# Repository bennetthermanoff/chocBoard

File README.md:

# chocBoard
PCB, ergogen, kicad files for chocBoard wireless split ergo keyboard
## [Learn more on my website](https://www.hermanoff.dev/content/chocBoard)

This repo contains the files to order a custom PCB for chocBoard, checkout my [zmk fork](https://github.com/xpsKING/zmk) to build firmware!

Read more about chocBoard on my [website](https://hermanoff.dev)

## LICENSE
This repo is attached with Attribution-NonCommercial-ShareAlike 4.0 International Creative Commons License, learn what his means [here](https://creativecommons.org/licenses/by-nc-sa/4.0/).

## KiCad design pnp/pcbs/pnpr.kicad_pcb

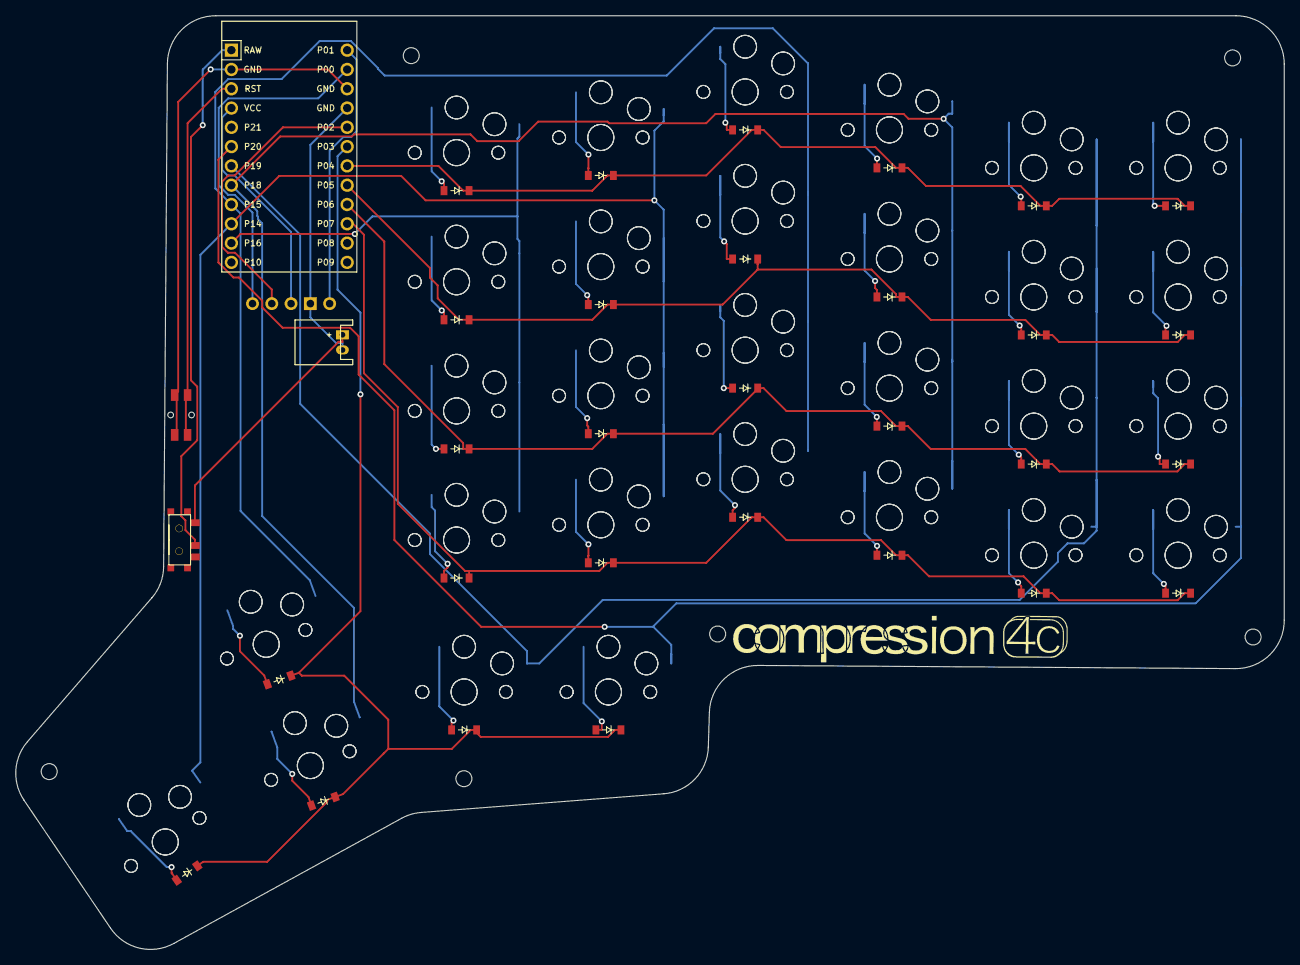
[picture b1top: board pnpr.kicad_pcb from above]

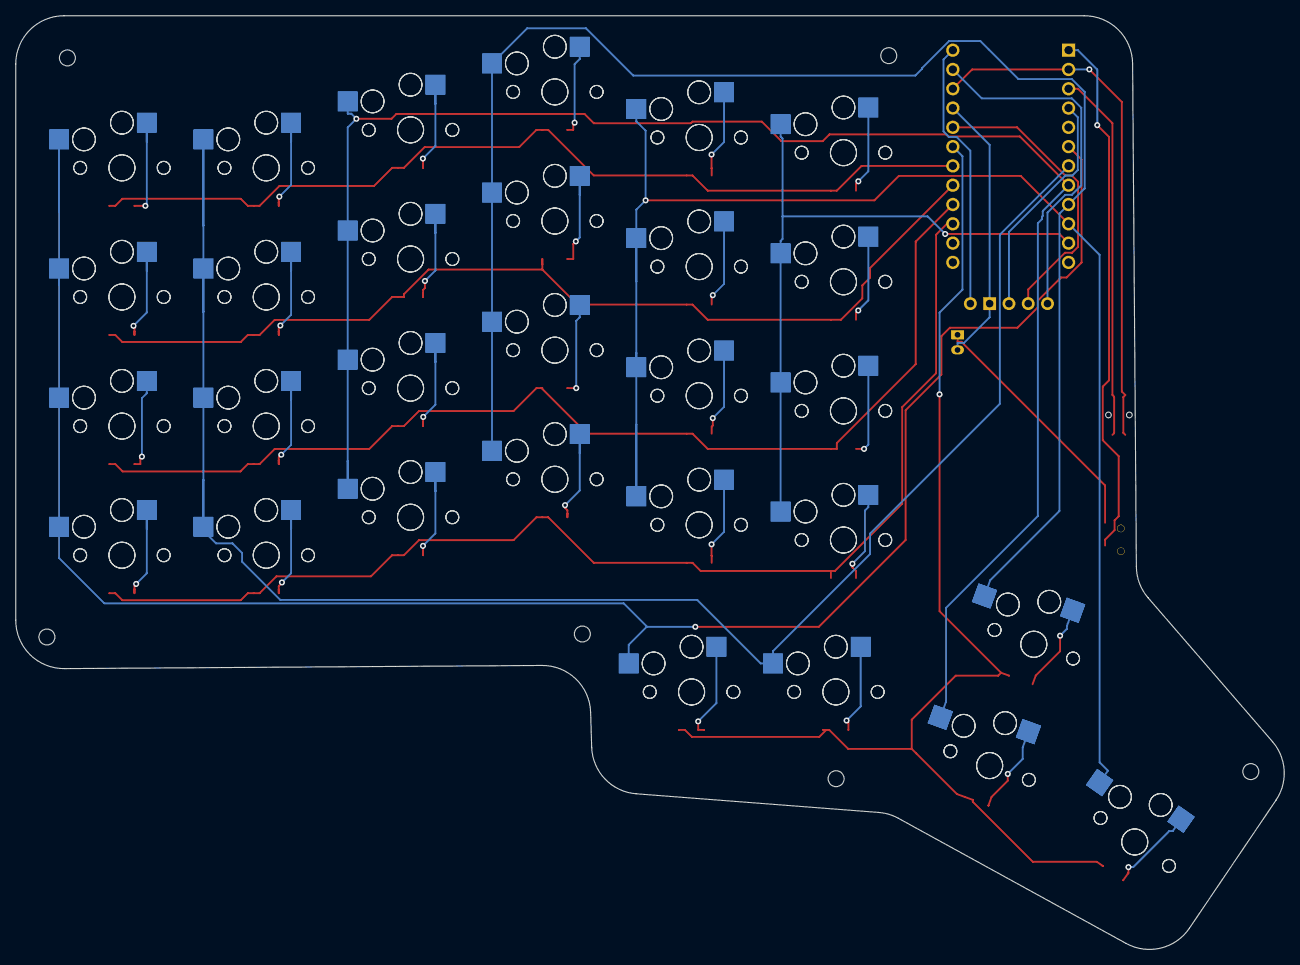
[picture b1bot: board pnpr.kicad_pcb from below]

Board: 2 copper layers, 167.0 x 122.9 mm, 92 parts (29 on the bottom side), 44 nets.

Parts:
D31, D34, D36, D37, D41, D49, D51, D52, D53, D54, D57, D58, D59, D61, D62, D64, D67, D68, D69, D71, D72, D73, D74, D75, D76, D77, D79, D84, D85: ComboDiode
JST1: JST_PH_S2B-PH-K_02x2.00mm_Angled
MCU1: ProMicro
OLED1: OLED; OLED_headers
Panasonic_EVQPUL_EVQPUC: Panasonic_EVQPUL_EVQPUC
S30, S31, S32, S33, S34, S35, S36, S37, S38, S39, S40, S41, S42, S43, S44, S45, S46, S47, S48, S49, S50, S51, S52, S53, S54, S55, S56, S57, S58, S59, S60, S61, S62, S63, S64, S65, S66, S67, S68, S69, S70, S71, S72, S73, S74, S75, S76, S77, S78, S79, S80, S81, S82, S83, S84, S85, S86, S87: PG1350
T1: SPDT_C128955

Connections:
Bplus: JST1.1, T1.1
GND: JST1.2, MCU1.2, MCU1.15, MCU1.16, Panasonic_EVQPUL_EVQPUC.1
P3: D54.1, D57.1, D58.1, D84.1, D85.1, MCU1.18
P4: D37.1, D41.1, D49.1, D53.1, D62.1, D74.1, MCU1.19
P5: D36.1, D52.1, D61.1, D69.1, D73.1, D77.1, MCU1.20
P6: D31.1, D51.1, D64.1, D68.1, D72.1, D76.1, MCU1.21
P7: D34.1, D59.1, D67.1, D71.1, D75.1, D79.1, MCU1.22
P14: MCU1.10, S46.2, S47.2, S48.2, S49.2, S58.2, S75.2, S76.2, S77.2, S78.2, S87.2
P15: MCU1.9, S42.2, S43.2, S44.2, S45.2, S57.2, S71.2, S72.2, S73.2, S74.2, S86.2
P16: MCU1.11, S50.2, S51.2, S52.2, S53.2, S79.2, S80.2, S81.2, S82.2
P18: MCU1.8, S38.2, S39.2, S40.2, S41.2, S56.2, S67.2, S68.2, S69.2, S70.2, S85.2
P19: MCU1.7, S34.2, S35.2, S36.2, S37.2, S55.2, S63.2, S64.2, S65.2, S66.2, S84.2
P20: MCU1.6, S30.2, S31.2, S32.2, S33.2, S54.2, S59.2, S60.2, S61.2, S62.2, S83.2
RAW: MCU1.1, T1.2
RST: MCU1.3, Panasonic_EVQPUL_EVQPUC.2
mirror_far_home: D58.2, S58.1, S87.1
mirror_home_home: D85.2, S56.1, S85.1
mirror_home_top: D57.2, S57.1, S86.1
mirror_index_bottom: D75.2, S46.1, S75.1
mirror_index_home: D76.2, S47.1, S76.1
mirror_index_num: D49.2, S49.1, S78.1
mirror_index_top: D77.2, S48.1, S77.1
mirror_inner_bottom: D79.2, S50.1, S79.1
mirror_inner_home: D51.2, S51.1, S80.1
mirror_inner_num: D53.2, S53.1, S82.1
mirror_inner_top: D52.2, S52.1, S81.1
mirror_middle_bottom: D71.2, S42.1, S71.1
mirror_middle_home: D72.2, S43.1, S72.1
mirror_middle_num: D74.2, S45.1, S74.1
mirror_middle_top: D73.2, S44.1, S73.1
mirror_near1_home: D54.2, S54.1, S83.1
mirror_near2_home: D84.2, S55.1, S84.1
mirror_outer_bottom: D59.2, S30.1, S59.1
mirror_outer_home: D31.2, S31.1, S60.1
mirror_outer_num: D62.2, S33.1, S62.1
mirror_outer_top: D61.2, S32.1, S61.1
mirror_pinky_bottom: D34.2, S34.1, S63.1
mirror_pinky_home: D64.2, S35.1, S64.1
mirror_pinky_num: D37.2, S37.1, S66.1
mirror_pinky_top: D36.2, S36.1, S65.1
mirror_ring_bottom: D67.2, S38.1, S67.1
mirror_ring_home: D68.2, S39.1, S68.1
mirror_ring_num: D41.2, S41.1, S70.1
mirror_ring_top: D69.2, S40.1, S69.1

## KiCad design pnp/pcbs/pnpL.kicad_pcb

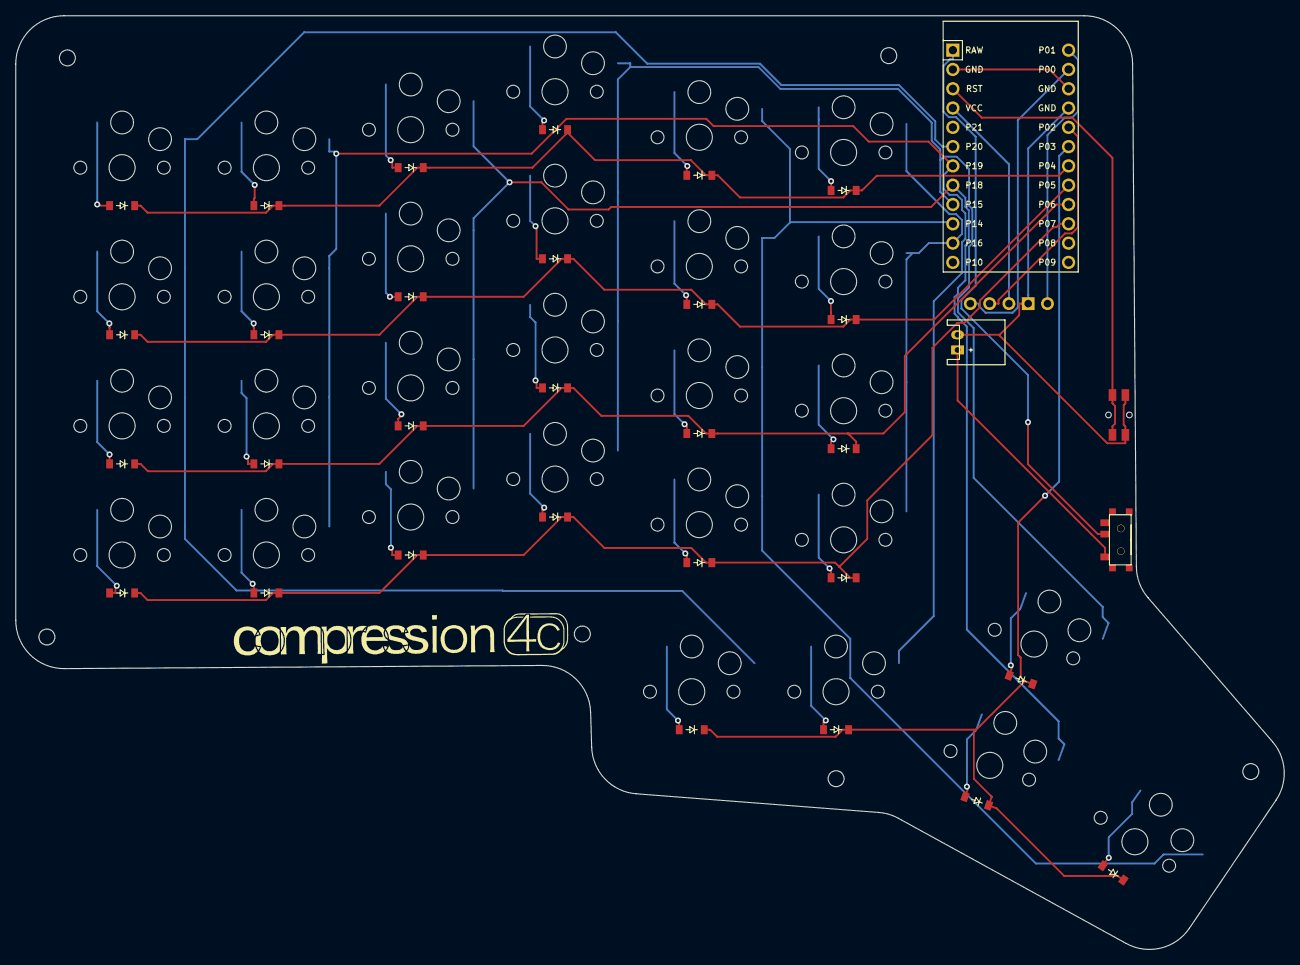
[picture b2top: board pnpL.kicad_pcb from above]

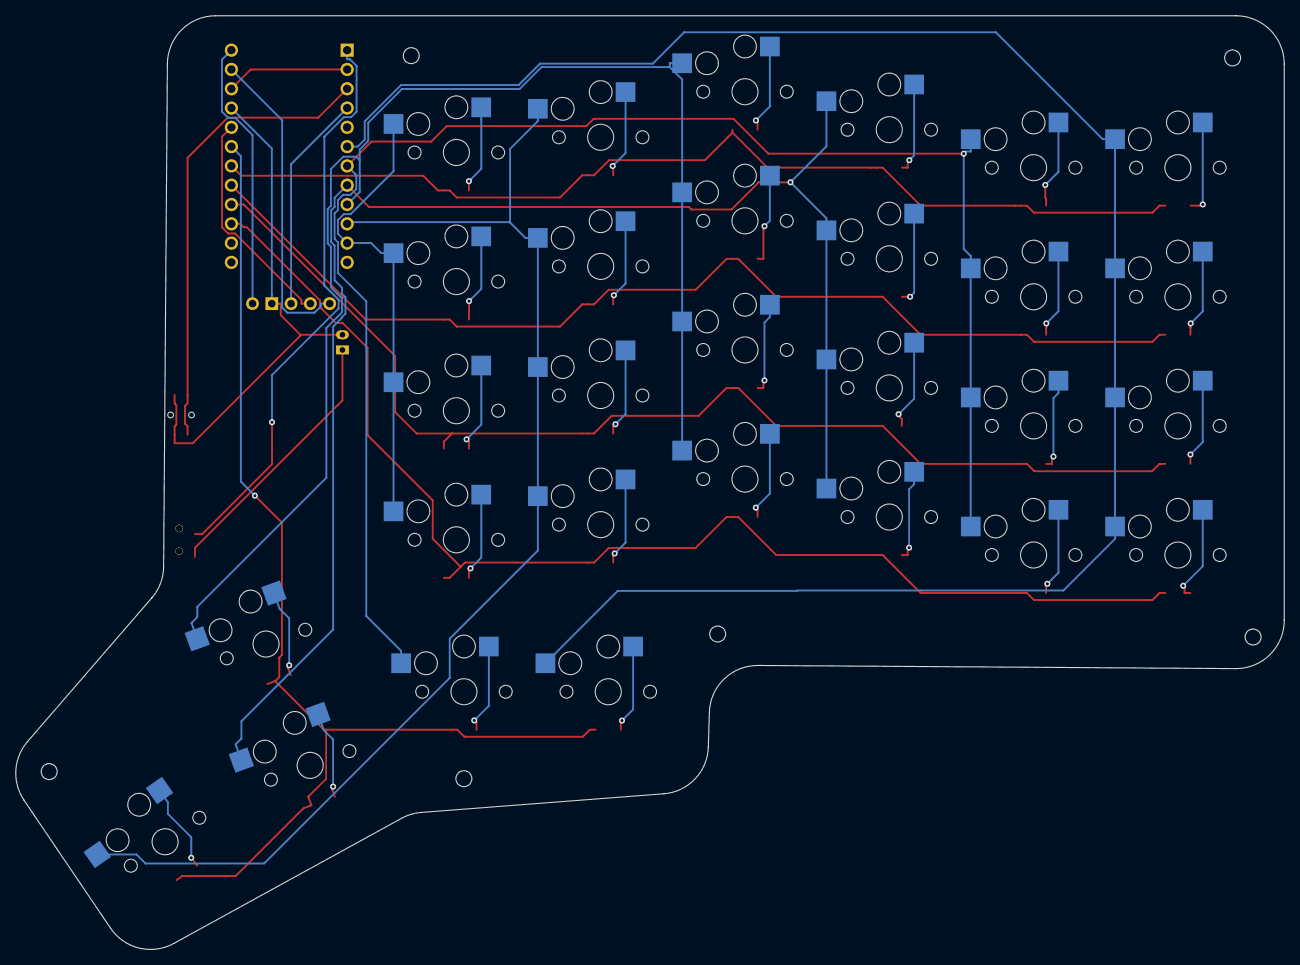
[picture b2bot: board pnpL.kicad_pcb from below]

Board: 2 copper layers, 167.0 x 122.9 mm, 63 parts (29 on the bottom side), 48 nets.

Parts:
D1, D2, D3, D4, D5, D6, D7, D8, D9, D10, D11, D12, D13, D14, D15, D16, D17, D18, D19, D20, D21, D22, D23, D24, D25, D26, D27, D28, D29: ComboDiode
JST1: JST_PH_S2B-PH-K_02x2.00mm_Angled
MCU1: ProMicro
OLED1: OLED; OLED_headers
Panasonic_EVQPUL_EVQPUC: Panasonic_EVQPUL_EVQPUC
S1, S2, S3, S4, S5, S6, S7, S8, S9, S10, S11, S12, S13, S14, S15, S16, S17, S18, S19, S20, S21, S22, S23, S24, S25, S26, S27, S28, S29: PG1350
T1: SPDT_C128955

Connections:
Bplus: JST1.1, T1.1
GND: JST1.2, MCU1.2, MCU1.15, MCU1.16, OLED1.1, Panasonic_EVQPUL_EVQPUC.1
P0: MCU1.14, OLED1.4
P1: MCU1.13, OLED1.0
P2: MCU1.17, OLED1.3
P3: D25.1, D26.1, D27.1, D28.1, D29.1, MCU1.18
P4: D4.1, D8.1, D12.1, D16.1, D20.1, D24.1, MCU1.19
P5: D3.1, D7.1, D11.1, D15.1, D19.1, D23.1, MCU1.20
P6: D2.1, D6.1, D10.1, D14.1, D18.1, D22.1, MCU1.21
P7: D1.1, D5.1, D9.1, D13.1, D17.1, D21.1, MCU1.22
P14: MCU1.10, S17.2, S18.2, S19.2, S20.2, S29.2
P15: MCU1.9, S13.2, S14.2, S15.2, S16.2, S28.2
P16: MCU1.11, S21.2, S22.2, S23.2, S24.2
P18: MCU1.8, S9.2, S10.2, S11.2, S12.2, S27.2
P19: MCU1.7, S5.2, S6.2, S7.2, S8.2, S26.2
P20: MCU1.6, S1.2, S2.2, S3.2, S4.2, S25.2
RAW: MCU1.1, T1.2
RST: MCU1.3, Panasonic_EVQPUL_EVQPUC.2
VCC: MCU1.4, OLED1.2
far_home: D29.2, S29.1
home_home: D27.2, S27.1
home_top: D28.2, S28.1
index_bottom: D17.2, S17.1
index_home: D18.2, S18.1
index_num: D20.2, S20.1
index_top: D19.2, S19.1
inner_bottom: D21.2, S21.1
inner_home: D22.2, S22.1
inner_num: D24.2, S24.1
inner_top: D23.2, S23.1
middle_bottom: D13.2, S13.1
middle_home: D14.2, S14.1
middle_num: D16.2, S16.1
middle_top: D15.2, S15.1
near1_home: D25.2, S25.1
near2_home: D26.2, S26.1
outer_bottom: D1.2, S1.1
outer_home: D2.2, S2.1
outer_num: D4.2, S4.1
outer_top: D3.2, S3.1
pinky_bottom: D5.2, S5.1
pinky_home: D6.2, S6.1
pinky_num: D8.2, S8.1
pinky_top: D7.2, S7.1
ring_bottom: D9.2, S9.1
ring_home: D10.2, S10.1
ring_num: D12.2, S12.1
ring_top: D11.2, S11.1

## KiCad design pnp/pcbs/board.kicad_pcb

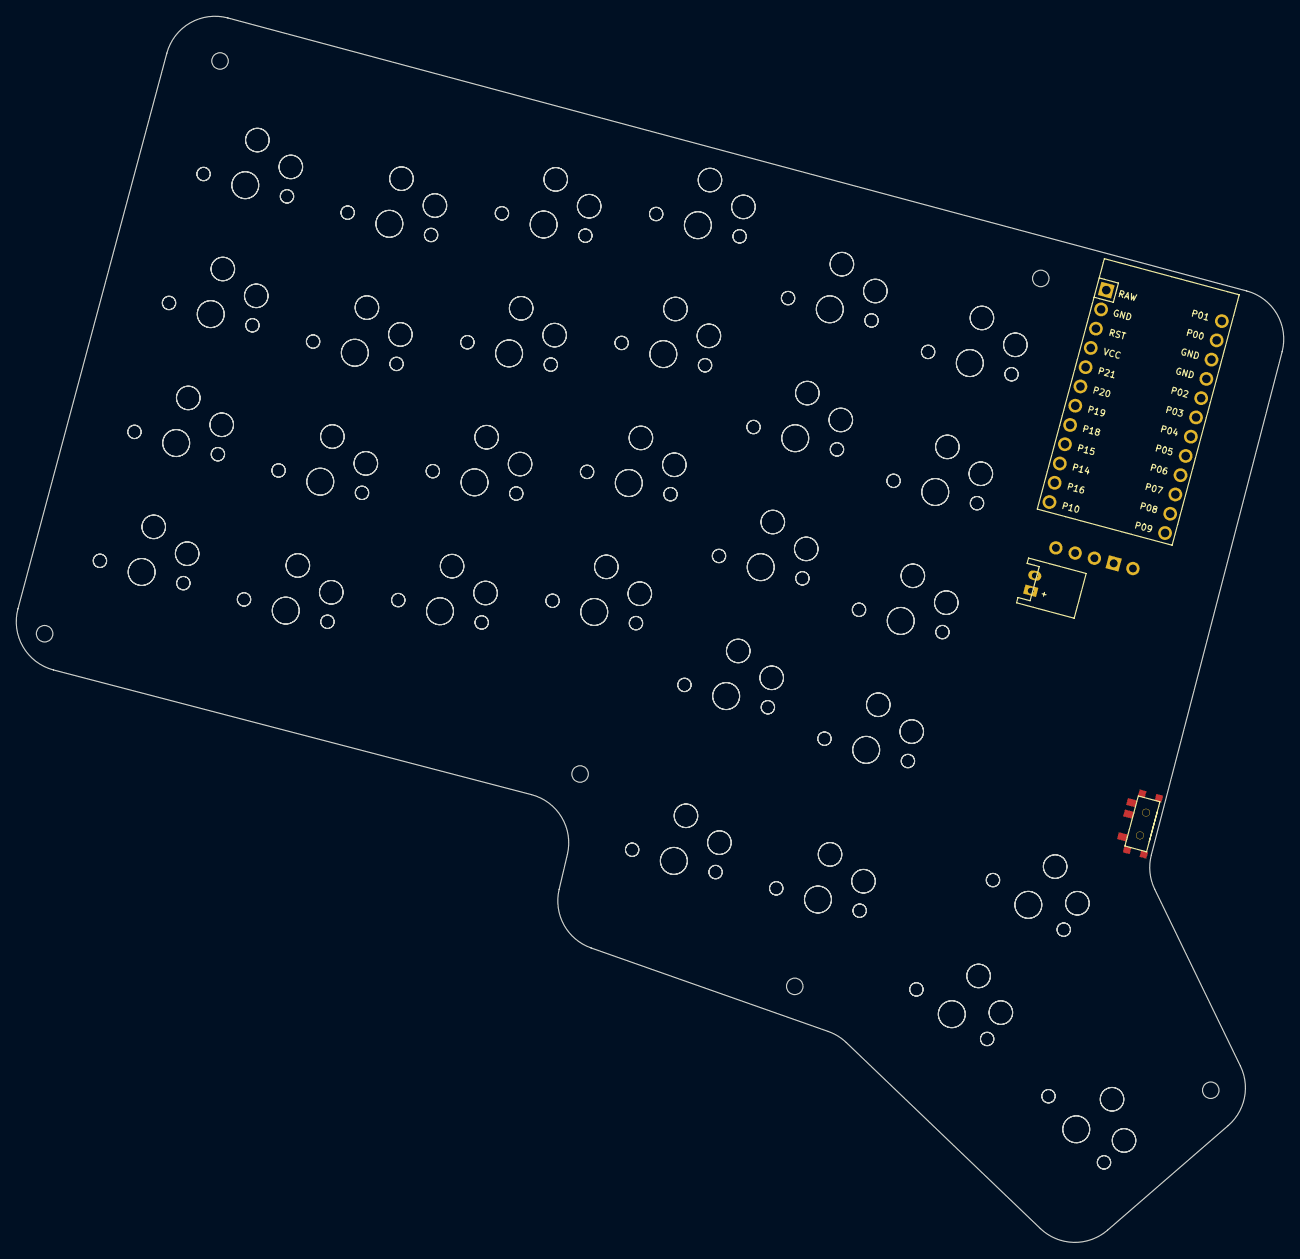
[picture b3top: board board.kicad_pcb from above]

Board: 2 copper layers, 161.4 x 156.2 mm, 236 parts (0 on the bottom side), 76 nets, no tracks yet.

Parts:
D1, D2, D3, D4, D5, D6, D7, D8, D9, D10, D11, D12, D13, D14, D15, D16, D17, D18, D19, D20, D21, D22, D23, D24, D25, D26, D27, D28, D29, D30, D31, D32, D33, D34, D35, D36, D37, D38, D39, D40, D41, D42, D43, D44, D45, D46, D47, D48, D49, D50, D51, D52, D53, D54, D55, D56, D57, D58, D59, D60, D61, D62, D63, D64, D65, D66, D67, D68, D69, D70, D71, D72, D73, D74, D75, D76, D77, D78, D79, D80, D81, D82, D83, D84, D85, D86, D87, D88, D89, D90, D91, D92, D93, D94, D95, D96, D97, D98, D99, D100, D101, D102, D103, D104, D105, D106, D107, D108, D109, D110, D111, D112, D113, D114, D115, D116: ComboDiode
JST1: JST_PH_S2B-PH-K_02x2.00mm_Angled
MCU1: ProMicro
OLED1: OLED; OLED_headers
S1, S2, S3, S4, S5, S6, S7, S8, S9, S10, S11, S12, S13, S14, S15, S16, S17, S18, S19, S20, S21, S22, S23, S24, S25, S26, S27, S28, S29, S30, S31, S32, S33, S34, S35, S36, S37, S38, S39, S40, S41, S42, S43, S44, S45, S46, S47, S48, S49, S50, S51, S52, S53, S54, S55, S56, S57, S58, S59, S60, S61, S62, S63, S64, S65, S66, S67, S68, S69, S70, S71, S72, S73, S74, S75, S76, S77, S78, S79, S80, S81, S82, S83, S84, S85, S86, S87, S88, S89, S90, S91, S92, S93, S94, S95, S96, S97, S98, S99, S100, S101, S102, S103, S104, S105, S106, S107, S108, S109, S110, S111, S112, S113, S114, S115, S116: PG1350
T1: SPDT_C128955

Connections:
Bplus: JST1.1, T1.1
GND: JST1.2, MCU1.2, MCU1.15, MCU1.16, OLED1.1
P0: MCU1.14, OLED1.4
P1: MCU1.13, OLED1.0
P2: MCU1.17, OLED1.3
P3: D25.1, D26.1, D27.1, D28.1, D29.1, D54.1, D55.1, D56.1, D57.1, D58.1, D83.1, D84.1, D85.1, D86.1, D87.1, D112.1, D113.1, D114.1, D115.1, D116.1, MCU1.18
P4: D4.1, D8.1, D12.1, D16.1, D20.1, D24.1, D33.1, D37.1, D41.1, D45.1, D49.1, D53.1, D62.1, D66.1, D70.1, D74.1, D78.1, D82.1, D91.1, D95.1, D99.1, D103.1, D107.1, D111.1, MCU1.19
P5: D3.1, D7.1, D11.1, D15.1, D19.1, D23.1, D32.1, D36.1, D40.1, D44.1, D48.1, D52.1, D61.1, D65.1, D69.1, D73.1, D77.1, D81.1, D90.1, D94.1, D98.1, D102.1, D106.1, D110.1, MCU1.20
P6: D2.1, D6.1, D10.1, D14.1, D18.1, D22.1, D31.1, D35.1, D39.1, D43.1, D47.1, D51.1, D60.1, D64.1, D68.1, D72.1, D76.1, D80.1, D89.1, D93.1, D97.1, D101.1, D105.1, D109.1, MCU1.21
P7: D1.1, D5.1, D9.1, D13.1, D17.1, D21.1, D30.1, D34.1, D38.1, D42.1, D46.1, D50.1, D59.1, D63.1, D67.1, D71.1, D75.1, D79.1, D88.1, D92.1, D96.1, D100.1, D104.1, D108.1, MCU1.22
P14: MCU1.10, S17.2, S18.2, S19.2, S20.2, S29.2, S46.2, S47.2, S48.2, S49.2, S58.2, S75.2, S76.2, S77.2, S78.2, S87.2, S104.2, S105.2, S106.2, S107.2, S116.2
P15: MCU1.9, S13.2, S14.2, S15.2, S16.2, S28.2, S42.2, S43.2, S44.2, S45.2, S57.2, S71.2, S72.2, S73.2, S74.2, S86.2, S100.2, S101.2, S102.2, S103.2, S115.2
P16: MCU1.11, S21.2, S22.2, S23.2, S24.2, S50.2, S51.2, S52.2, S53.2, S79.2, S80.2, S81.2, S82.2, S108.2, S109.2, S110.2, S111.2
P18: MCU1.8, S9.2, S10.2, S11.2, S12.2, S27.2, S38.2, S39.2, S40.2, S41.2, S56.2, S67.2, S68.2, S69.2, S70.2, S85.2, S96.2, S97.2, S98.2, S99.2, S114.2
P19: MCU1.7, S5.2, S6.2, S7.2, S8.2, S26.2, S34.2, S35.2, S36.2, S37.2, S55.2, S63.2, S64.2, S65.2, S66.2, S84.2, S92.2, S93.2, S94.2, S95.2, S113.2
P20: MCU1.6, S1.2, S2.2, S3.2, S4.2, S25.2, S30.2, S31.2, S32.2, S33.2, S54.2, S59.2, S60.2, S61.2, S62.2, S83.2, S88.2, S89.2, S90.2, S91.2, S112.2
RAW: MCU1.1, T1.2
VCC: MCU1.4, OLED1.2
far_home: D29.2, D116.2, S29.1, S116.1
home_home: D27.2, D114.2, S27.1, S114.1
home_top: D28.2, D115.2, S28.1, S115.1
index_bottom: D17.2, D104.2, S17.1, S104.1
index_home: D18.2, D105.2, S18.1, S105.1
index_num: D20.2, D107.2, S20.1, S107.1
index_top: D19.2, D106.2, S19.1, S106.1
inner_bottom: D21.2, D108.2, S21.1, S108.1
inner_home: D22.2, D109.2, S22.1, S109.1
inner_num: D24.2, D111.2, S24.1, S111.1
inner_top: D23.2, D110.2, S23.1, S110.1
middle_bottom: D13.2, D100.2, S13.1, S100.1
middle_home: D14.2, D101.2, S14.1, S101.1
middle_num: D16.2, D103.2, S16.1, S103.1
middle_top: D15.2, D102.2, S15.1, S102.1
mirror_far_home: D58.2, D87.2, S58.1, S87.1
mirror_home_home: D56.2, D85.2, S56.1, S85.1
mirror_home_top: D57.2, D86.2, S57.1, S86.1
mirror_index_bottom: D46.2, D75.2, S46.1, S75.1
mirror_index_home: D47.2, D76.2, S47.1, S76.1
mirror_index_num: D49.2, D78.2, S49.1, S78.1
mirror_index_top: D48.2, D77.2, S48.1, S77.1
mirror_inner_bottom: D50.2, D79.2, S50.1, S79.1
mirror_inner_home: D51.2, D80.2, S51.1, S80.1
mirror_inner_num: D53.2, D82.2, S53.1, S82.1
mirror_inner_top: D52.2, D81.2, S52.1, S81.1
mirror_middle_bottom: D42.2, D71.2, S42.1, S71.1
mirror_middle_home: D43.2, D72.2, S43.1, S72.1
mirror_middle_num: D45.2, D74.2, S45.1, S74.1
mirror_middle_top: D44.2, D73.2, S44.1, S73.1
mirror_near1_home: D54.2, D83.2, S54.1, S83.1
mirror_near2_home: D55.2, D84.2, S55.1, S84.1
mirror_outer_bottom: D30.2, D59.2, S30.1, S59.1
mirror_outer_home: D31.2, D60.2, S31.1, S60.1
mirror_outer_num: D33.2, D62.2, S33.1, S62.1
mirror_outer_top: D32.2, D61.2, S32.1, S61.1
mirror_pinky_bottom: D34.2, D63.2, S34.1, S63.1
mirror_pinky_home: D35.2, D64.2, S35.1, S64.1
mirror_pinky_num: D37.2, D66.2, S37.1, S66.1
mirror_pinky_top: D36.2, D65.2, S36.1, S65.1
mirror_ring_bottom: D38.2, D67.2, S38.1, S67.1
mirror_ring_home: D39.2, D68.2, S39.1, S68.1
mirror_ring_num: D41.2, D70.2, S41.1, S70.1
mirror_ring_top: D40.2, D69.2, S40.1, S69.1
near1_home: D25.2, D112.2, S25.1, S112.1
near2_home: D26.2, D113.2, S26.1, S113.1
outer_bottom: D1.2, D88.2, S1.1, S88.1
outer_home: D2.2, D89.2, S2.1, S89.1
outer_num: D4.2, D91.2, S4.1, S91.1
outer_top: D3.2, D90.2, S3.1, S90.1
pinky_bottom: D5.2, D92.2, S5.1, S92.1
pinky_home: D6.2, D93.2, S6.1, S93.1
pinky_num: D8.2, D95.2, S8.1, S95.1
pinky_top: D7.2, D94.2, S7.1, S94.1
ring_bottom: D9.2, D96.2, S9.1, S96.1
ring_home: D10.2, D97.2, S10.1, S97.1
ring_num: D12.2, D99.2, S12.1, S99.1
ring_top: D11.2, D98.2, S11.1, S98.1

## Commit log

2022-11-29 init
2022-11-29 some changes, some errors
2022-11-29 thumb cluster shifted down
2022-12-26 forced submodule
    nice view
    ergogen
    submod
2023-01-10 migrate ergogen 4
2023-01-10 ergogen 4 (broken config tho)
2023-01-10 v4 migration complete
2023-01-10 deleted old footprints
2023-01-24 holes
2023-01-25 new onoff and placements
2023-05-03 release
2023-05-03 Release!
2023-05-08 Create LICENSE
2023-05-09 dualside complete
2023-05-09 pnp l and r
2023-05-19 v1 prototype gerber ordered
